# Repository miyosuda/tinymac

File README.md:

## About

This is my study project for disigning PCB with creating tiny old macintosh like toy.

## License

Firmware and Tools code is licensed under Apache License, Version 2.0

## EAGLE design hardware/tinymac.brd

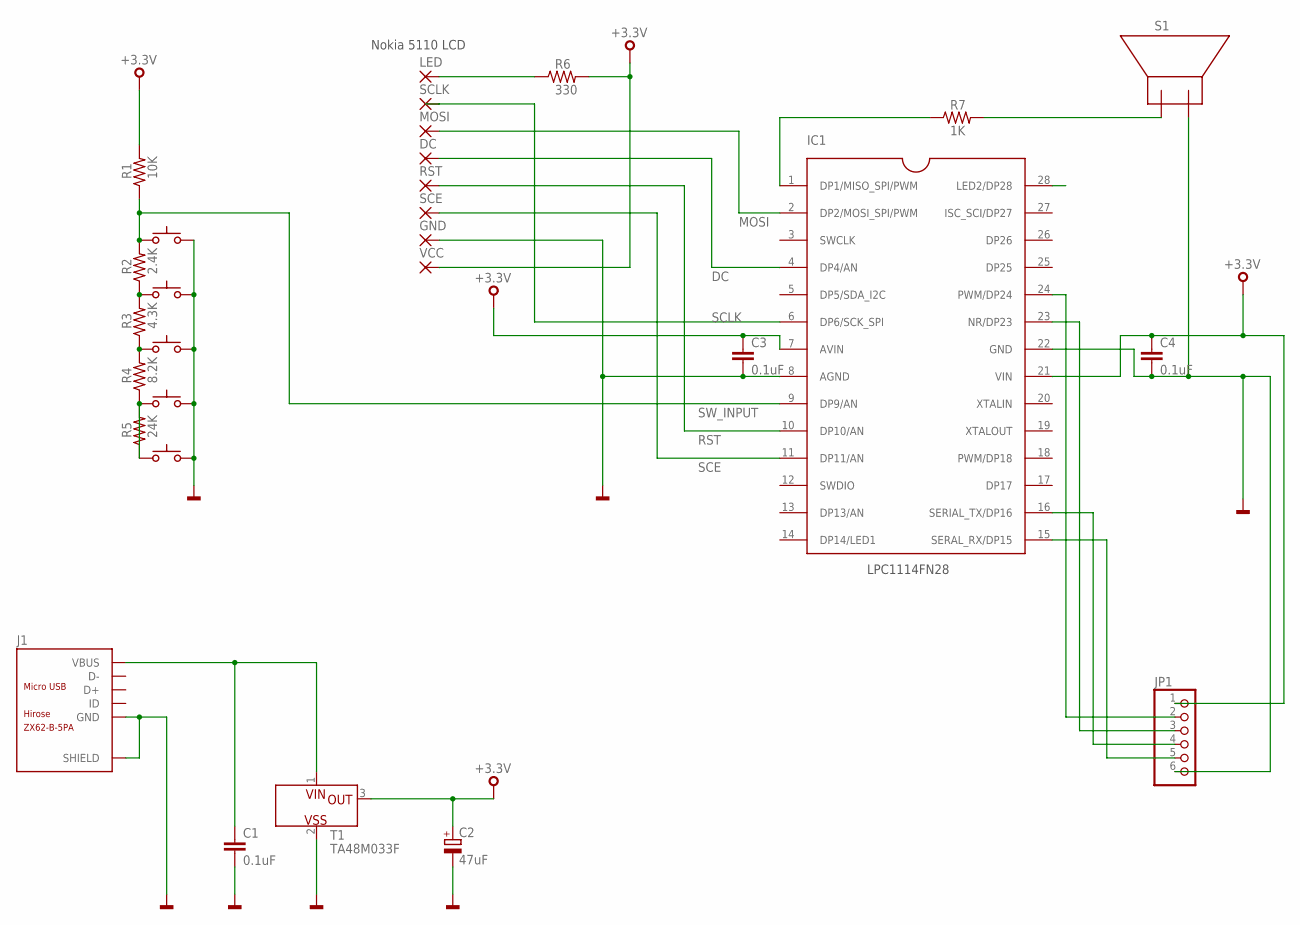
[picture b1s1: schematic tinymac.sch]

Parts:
C1, C3, C4: 0.1uF; C025-024X044
C2: 47uF; E2,5-5
DC: HOLE_PAD
GND: HOLE_PAD
IC1: LPC1114FN28; DIP28
J1: ZX62-B-5PA; ZX62-B-5PA(11)
JP1: PINHD-1X6_2.54; 1X06
LED: HOLE_PAD
MOSI: HOLE_PAD
R1: 10K; 0207/2V
R2: 2.4K; 0207/2V
R3: 4.3K; 0207/2V
R4: 8.2K; 0207/2V
R5: 24K; 0207/2V
R6: 330; 0207/2V
R7: 1K; 0207/2V
RST: HOLE_PAD
S1: PKM13EPYH4000
SCE: HOLE_PAD
SCLK: HOLE_PAD
SW1, SW2, SW3, SW4, SW5: TACT_SW
T1: TA48M033F
VCC: HOLE_PAD

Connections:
+3.3V: C2.+, C3.1, C4.1, IC1.7 (AVIN), IC1.21 (VIN), JP1.1, R1.2, R6.2, T1.3 (OUT), VCC.1
DC: DC.1, IC1.4 (DP4/AN)
GND: C1.2, C2.-, C3.2, C4.2, GND.1, IC1.8 (AGND), IC1.22 (GND), J1.5 (GND), J1.SH1 (SHIELD), J1.SH2 (SHIELD), J1.SH3 (SHIELD), J1.SH4 (SHIELD), J1.SH5 (SHIELD), J1.SH6 (SHIELD), JP1.6, S1.2, SW1.1-B, SW1.2-B, SW2.1-B, SW2.2-B, SW3.1-B, SW3.2-B, SW4.1-B, SW4.2-B, SW5.1-B, SW5.2-B, T1.2 (VSS)
MOSI: IC1.2 (DP2/MOSI_SPI/PWM), MOSI.1
unnamed: IC1.15 (SERAL_RX/DP15), JP1.5
unnamed: R2.2, R3.2, SW2.1-A, SW2.2-A
unnamed: IC1.16 (SERIAL_TX/DP16), JP1.4
unnamed: R3.1, R4.2, SW3.1-A, SW3.2-A
unnamed: R4.1, R5.1, SW4.1-A, SW4.2-A
unnamed: R5.2, SW5.1-A, SW5.2-A
unnamed: IC1.1 (DP1/MISO_SPI/PWM), R7.1
unnamed: R7.2, S1.1
unnamed: IC1.24 (PWM/DP24), JP1.2
unnamed: IC1.23 (NR/DP23), JP1.3
unnamed: LED.1, R6.1
RST: IC1.10 (DP10/AN), RST.1
SCE: IC1.11 (DP11/AN), SCE.1
SCLK: IC1.6 (DP6/SCK_SPI), SCLK.1
SW_INPUT: IC1.9 (DP9/AN), R1.1, R2.1, SW1.1-A, SW1.2-A
VBUS: C1.1, J1.1 (VBUS), T1.1 (VIN)

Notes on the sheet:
Nokia 5110 LCD
LPC1114FN28

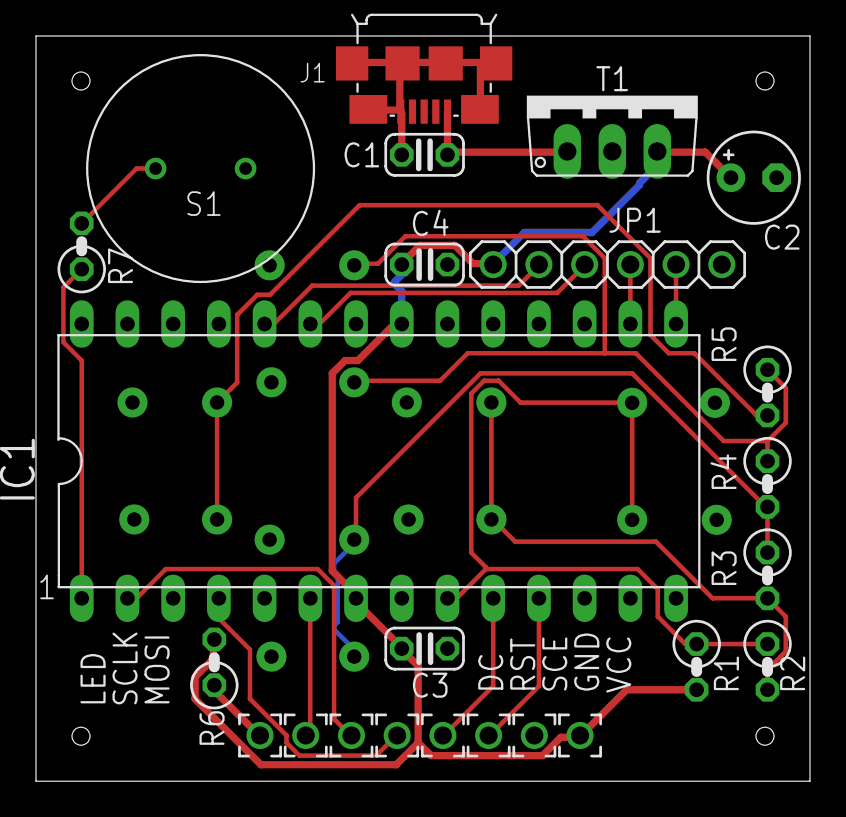
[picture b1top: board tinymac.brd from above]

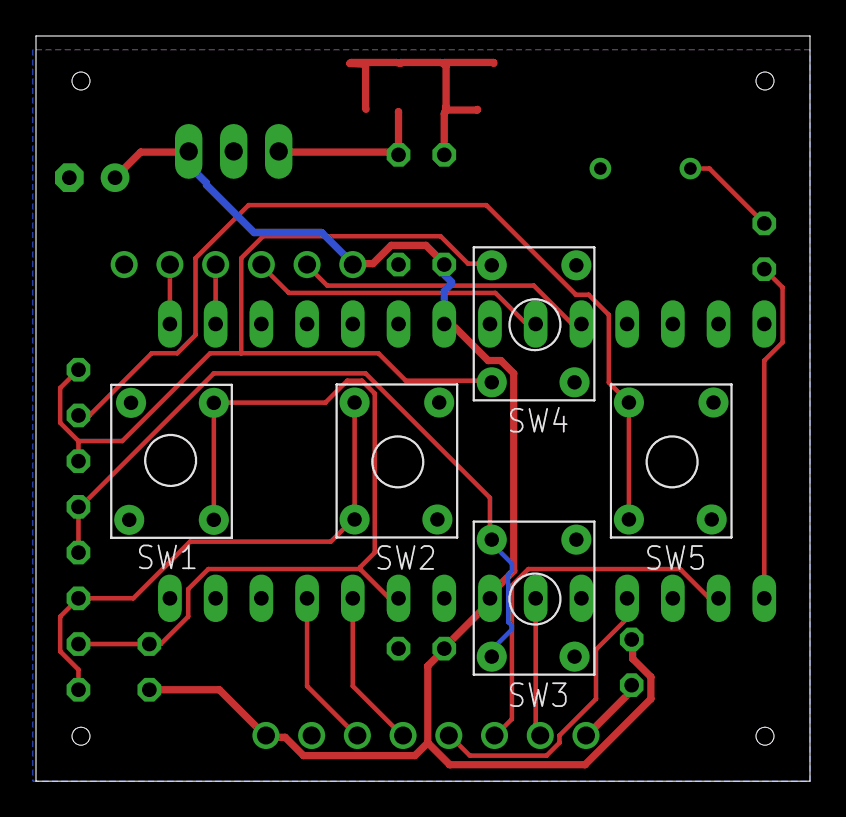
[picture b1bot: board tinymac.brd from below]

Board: 2 copper layers, 43.0 x 41.4 mm, 29 parts (5 on the bottom side), 20 nets.

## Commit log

2014-08-30 add initial tinymac files
2014-08-30 added firmware and tools code license
2014-08-30 edit board net
2014-08-31 try full GND
2014-08-31 set Seeed DRC setting
2014-08-31 add screw hole
2014-08-31 fix board register position overlap
2014-08-31 copy Electorolytic Capacitor Device to tinymac.lbr
2014-08-31 replace capacitor C2
2014-09-02 move full GND to bottom layer
2014-09-03 set net classes properties
2014-09-03 adjust route and add restrict area around screw hole
2014-09-03 change eagleup output setting
2014-09-05 change DRU setting to Seeed-2layer-DRU
2014-09-06 apply pin setting in firmware code as schematic
2014-09-06 add gerver data of the board
2014-09-06 add script for FusionPCB zip file packing
2014-09-07 add tinymac toy image
2014-09-07 add chip name notation in schematic
2014-09-07 change drill hole position
2014-09-30 add large mac smile face
2014-11-25 add library, BS84, LPC11U, LD1117
2014-11-25 LPC11U35 chip library fix
2014-11-25 fix LPC11U35/FBD48/401 device name
